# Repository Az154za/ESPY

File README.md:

# ESPY:
The main mcu is the esp32-P4 that allows fast lane data transmission allowing the camera and display option .
This project contains 4 layers 2 for signals 1 for 3V3 and one for Ground .  

The reason I chose the p4 is because it's very good for cameras .

-- feel free to grab gerber file and to print them yourself --
# Schematic :

# Routing :

# 3D overview : 

# BOM ( visual ) 

Total:192$

I hope you like this project

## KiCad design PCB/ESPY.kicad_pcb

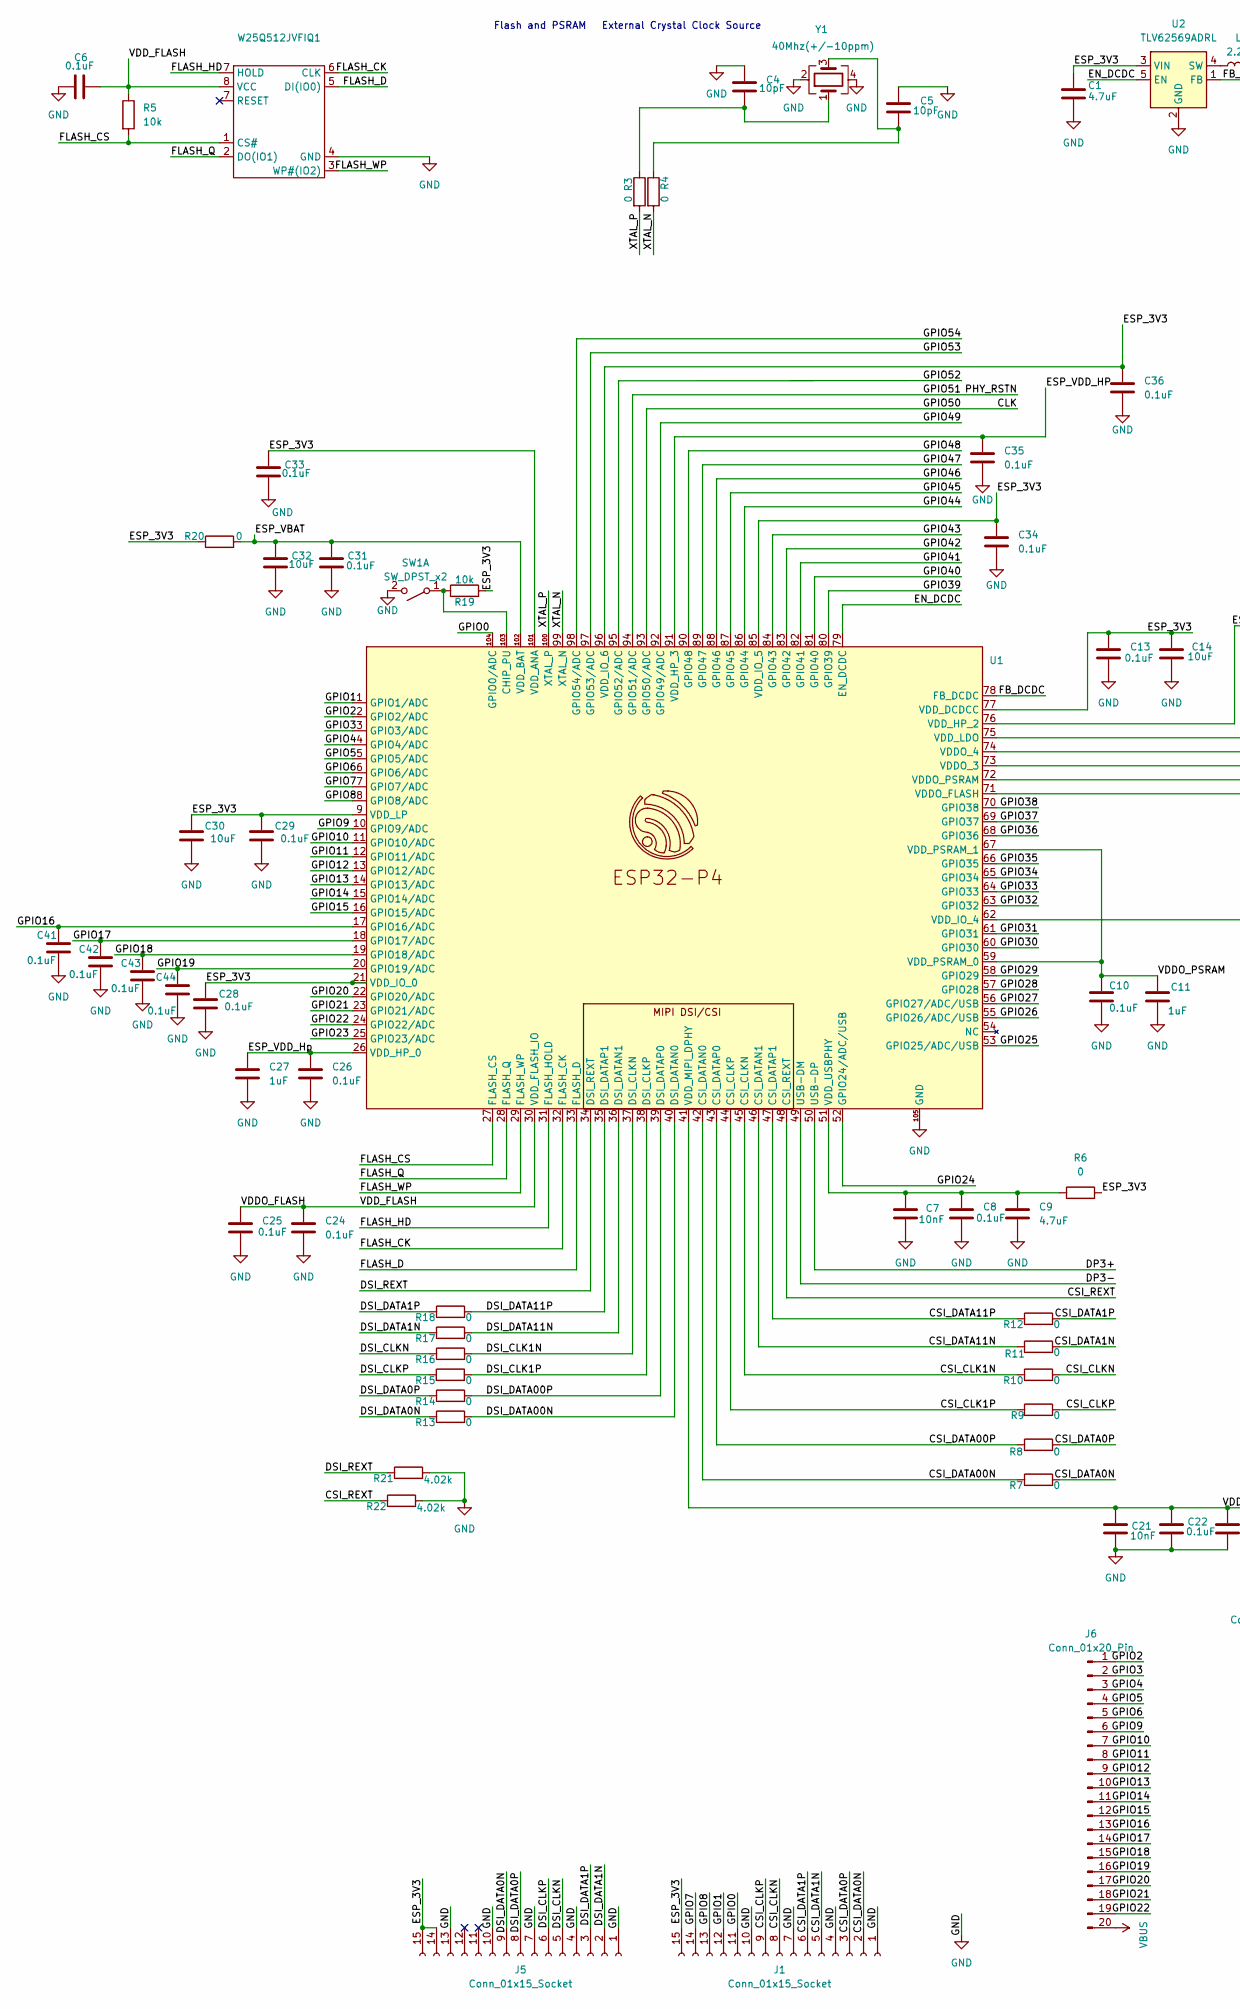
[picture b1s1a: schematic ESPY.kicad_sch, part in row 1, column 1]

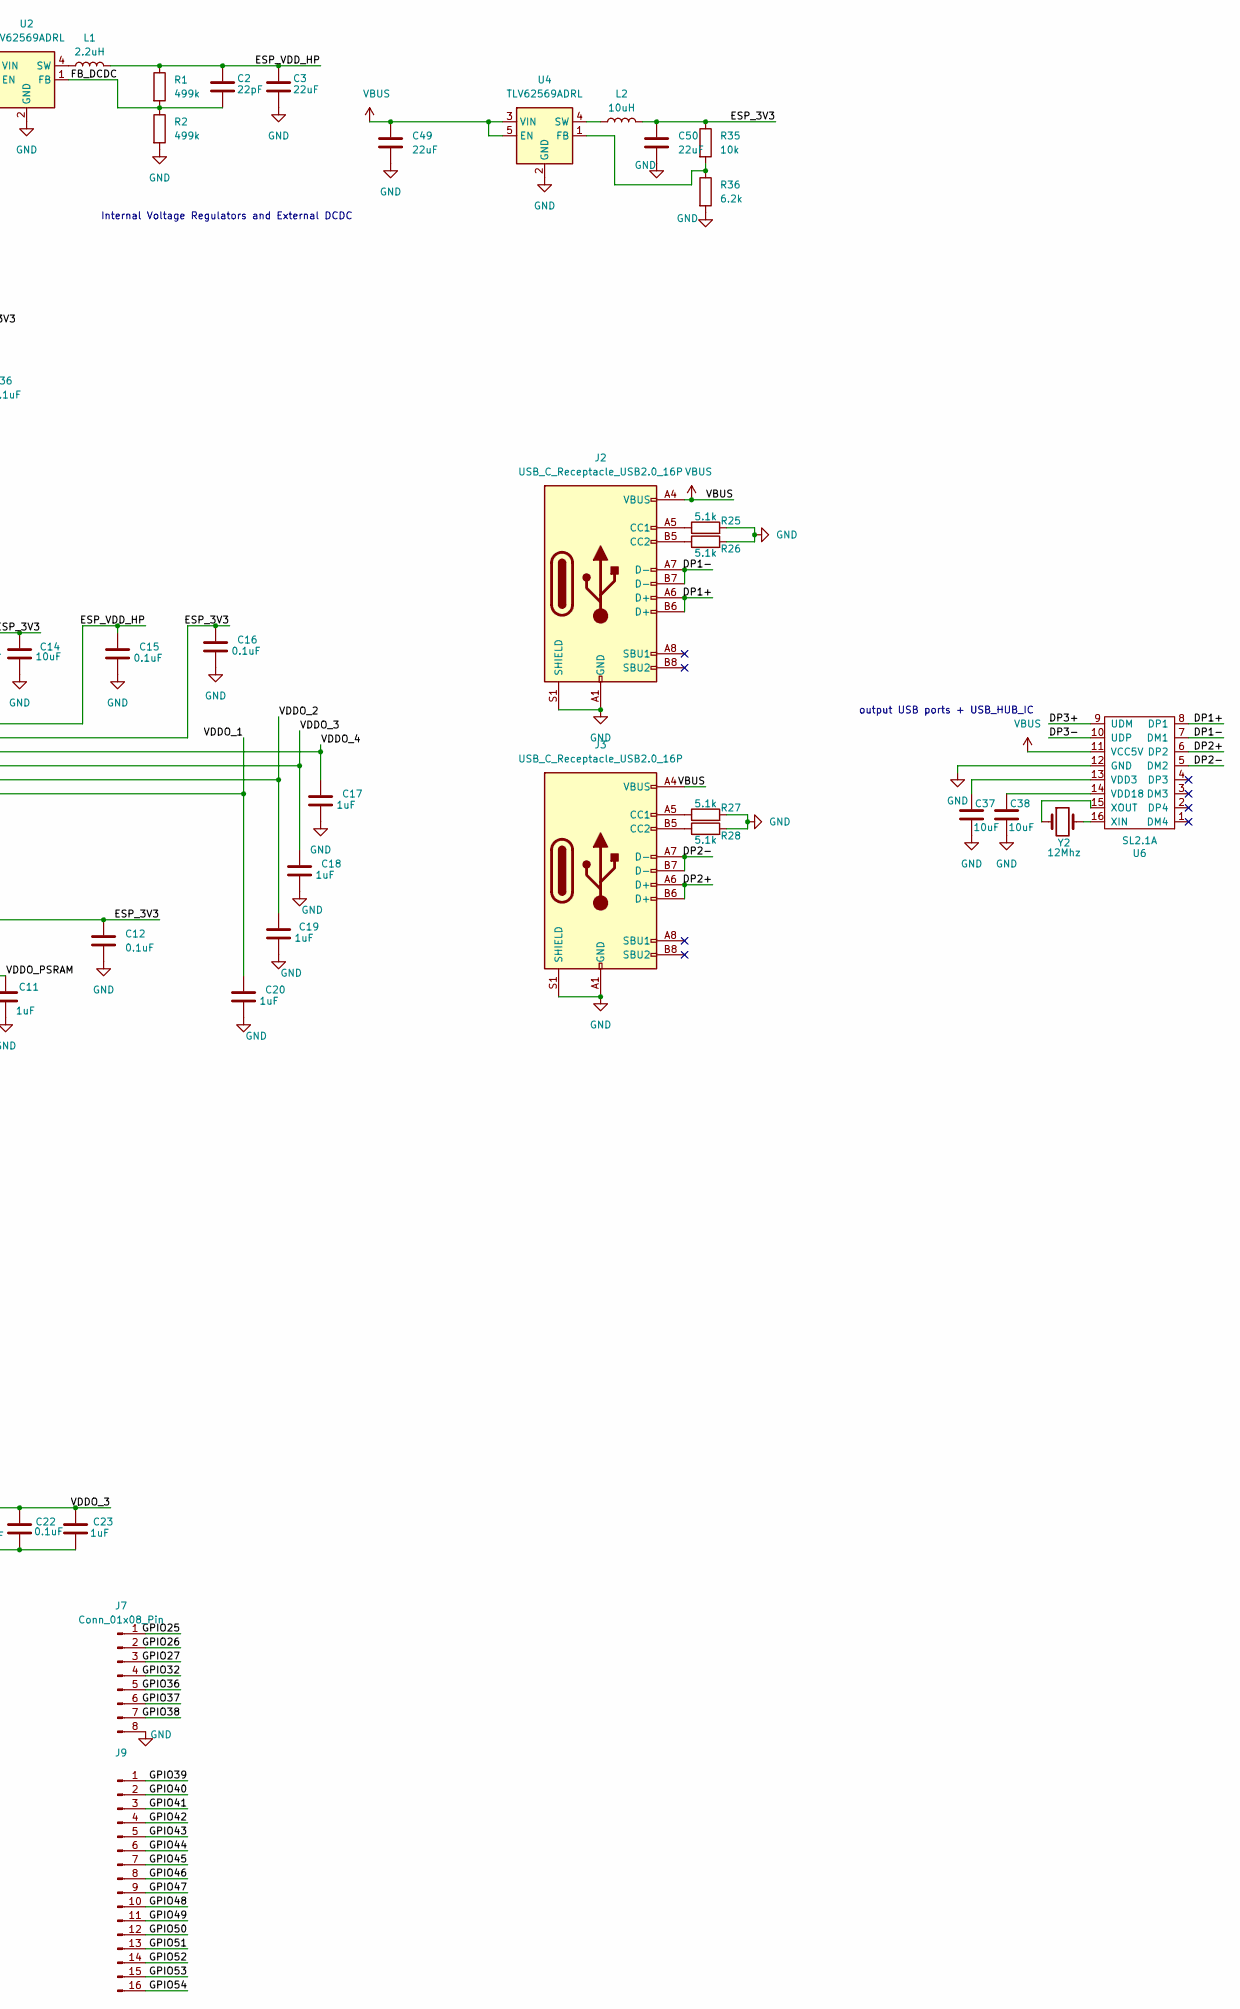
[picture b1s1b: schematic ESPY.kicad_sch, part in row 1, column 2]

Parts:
C1, C9: 4.7uF; C_0402_1005Metric
C2: 22pF; C_0402_1005Metric
C3, C49, C50: 22uF; C_0402_1005Metric
C4, C5: 10pF; C_0402_1005Metric
C6, C8, C10, C12, C13, C15, C16, C22, C24, C25, C26, C28, C29, C31, C33, C34, C35, C36, C41, C42, C43, C44: 0.1uF; C_0402_1005Metric
C7, C21: 10nF; C_0402_1005Metric
C11, C17, C18, C19, C20, C23, C27: 1uF; C_0402_1005Metric
C14, C30, C32, C37, C38: 10uF; C_0402_1005Metric
J1, J5: Conn_01x15_Socket; Molex_502244-1530_1x15-1MP_P0.5mm_Horizontal
J2, J3: USB_C_Receptacle_USB2.0_16P; USB_C_Receptacle_GCT_USB4105-xx-A_16P_TopMnt_Horizontal
J6: Conn_01x20_Pin; PinHeader_2x10_P2.54mm_Vertical
J7: Conn_01x08_Pin; PinHeader_1x08_P2.54mm_Vertical
J9: Conn_01x16_Pin; PinHeader_2x08_P2.54mm_Vertical
L1: 2.2uH; L_0402_1005Metric
L2: 10uH; L_0603_1608Metric
R1, R2: 499k; R_0402_1005Metric
R3, R4, R6, R7, R8, R9, R10, R11, R12, R13, R14, R15, R16, R17, R18, R20: 0; R_0402_1005Metric
R5, R19, R35: 10k; R_0402_1005Metric
R21, R22: 4.02k; R_0402_1005Metric
R25, R26, R27, R28: 5.1k; R_0402_1005Metric
R36: 6.2k; R_0402_1005Metric
SW1: SW_DPST_x2; SW_Push_SPST_NO_Alps_SKRK
U1: ESP32-P4
U2, U4: TLV62569ADRL; SOT-563
U6: SL2.1A; SOIC-16_4.55x10.3mm_P1.27mm
W25Q512JVFIQ1: SOIC-16W_7.5x10.3mm_P1.27mm
Y1: 40Mhz(+/-10ppm); Oscillator_SMD_Abracon_ASE-4Pin_3.2x2.5mm
Y2: 12Mhz; Crystal_SMD_3215-2Pin_3.2x1.5mm

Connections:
/CLK: J9.12, U1.93 (GPIO50/ADC)
/CSI_CLK1N: R10.1, U1.45 (CSI_CLKN)
/CSI_CLK1P: R9.1, U1.44 (CSI_CLKP)
/CSI_CLKN: J1.8, R10.2
/CSI_CLKP: J1.9, R9.2
/CSI_DATA00N: R7.1, U1.42 (CSI_DATAN0)
/CSI_DATA0N: J1.2, R7.2
/CSI_DATA00P: R8.1, U1.43 (CSI_DATAP0)
/CSI_DATA0P: J1.3, R8.2
/CSI_DATA1N: J1.5, R11.2
/CSI_DATA1P: J1.6, R12.2
/CSI_DATA11N: R11.1, U1.46 (CSI_DATAN1)
/CSI_DATA11P: R12.1, U1.47 (CSI_DATAP1)
/CSI_REXT: R22.1, U1.48 (CSI_REXT)
/DP1+: J2.A6 (D+), J2.B6 (D+), U6.8 (DP1)
/DP1-: J2.A7 (D-), J2.B7 (D-), U6.7 (DM1)
/DP2+: J3.A6 (D+), J3.B6 (D+), U6.6 (DP2)
/DP2-: J3.A7 (D-), J3.B7 (D-), U6.5 (DM2)
/DP3+: U1.50 (USB-DP), U6.9 (UDM)
/DP3-: U1.49 (USB-DM), U6.10 (UDP)
/DSI_CLK1N: R16.2, U1.37 (DSI_CLKN)
/DSI_CLK1P: R15.2, U1.38 (DSI_CLKP)
/DSI_CLKN: J5.5, R16.1
/DSI_CLKP: J5.6, R15.1
/DSI_DATA0N: J5.9, R13.1
/DSI_DATA00N: R13.2, U1.40 (DSI_DATAN0)
/DSI_DATA0P: J5.8, R14.1
/DSI_DATA00P: R14.2, U1.39 (DSI_DATAP0)
/DSI_DATA1N: J5.2, R17.1
/DSI_DATA1P: J5.3, R18.1
/DSI_DATA11N: R17.2, U1.36 (DSI_DATAN1)
/DSI_DATA11P: R18.2, U1.35 (DSI_DATAP1)
/DSI_REXT: R21.1, U1.34 (DSI_REXT)
/EN_DCDC: U1.79 (EN_DCDC), U2.5 (EN)
/ESP_3V3: C1.1, C12.1, C13.1, C14.1, C16.1, C28.1, C29.1, C30.1, C33.1, C34.1, C36.1, C50.1, J1.15, J5.14, J5.15, L2.2, R6.2, R19.2, R20.1, R35.1, U1.9 (VDD_LP), U1.21 (VDD_IO_0), U1.62 (VDD_IO_4), U1.75 (VDD_LDO), U1.77 (VDD_DCDCC), U1.85 (VDD_IO_5), U1.96 (VDD_IO_6), U1.101 (VDD_ANA), U2.3 (VIN)
/ESP_VBAT: C31.1, C32.1, R20.2, U1.102 (VDD_BAT)
/ESP_VDD_HP: C2.1, C3.1, C15.1, C35.1, L1.2, R1.1, U1.76 (VDD_HP_2), U1.91 (VDD_HP_3)
/ESP_VDD_Hp: C26.1, C27.1, U1.26 (VDD_HP_0)
/FB_DCDC: C2.2, R1.2, R2.1, U1.78 (FB_DCDC), U2.1 (FB)
/FLASH_CK: U1.32 (FLASH_CK), W25Q512JVFIQ1.6 (CLK)
/FLASH_CS: R5.2, U1.27 (FLASH_CS), W25Q512JVFIQ1.1 (CS#)
/FLASH_D: U1.33 (FLASH_D), W25Q512JVFIQ1.5 (DI(IO0))
/FLASH_HD: U1.31 (FLASH_HOLD), W25Q512JVFIQ1.7 (HOLD)
/FLASH_Q: U1.28 (FLASH_Q), W25Q512JVFIQ1.2 (DO(IO1))
/FLASH_WP: U1.29 (FLASH_WP), W25Q512JVFIQ1.3 (WP#(IO2))
/GPIO0: J1.11, U1.104 (GPIO0/ADC)
/GPIO1: J1.12, U1.1 (GPIO1/ADC)
/GPIO2: J6.1, U1.2 (GPIO2/ADC)
/GPIO3: J6.2, U1.3 (GPIO3/ADC)
/GPIO4: J6.3, U1.4 (GPIO4/ADC)
/GPIO5: J6.4, U1.5 (GPIO5/ADC)
/GPIO6: J6.5, U1.6 (GPIO6/ADC)
/GPIO7: J1.14, U1.7 (GPIO7/ADC)
/GPIO8: J1.13, U1.8 (GPIO8/ADC)
/GPIO9: J6.6, U1.10 (GPIO9/ADC)
/GPIO10: J6.7, U1.11 (GPIO10/ADC)
/GPIO11: J6.8, U1.12 (GPIO11/ADC)
/GPIO12: J6.9, U1.13 (GPIO12/ADC)
/GPIO13: J6.10, U1.14 (GPIO13/ADC)
/GPIO14: J6.11, U1.15 (GPIO14/ADC)
/GPIO15: J6.12, U1.16 (GPIO15/ADC)
/GPIO16: C41.1, J6.13, U1.17 (GPIO16/ADC)
/GPIO17: C42.1, J6.14, U1.18 (GPIO17/ADC)
/GPIO18: C43.1, J6.15, U1.19 (GPIO18/ADC)
/GPIO19: C44.1, J6.16, U1.20 (GPIO19/ADC)
/GPIO20: J6.17, U1.22 (GPIO20/ADC)
/GPIO21: J6.18, U1.23 (GPIO21/ADC)
/GPIO22: J6.19, U1.24 (GPIO22/ADC)
/GPIO23: U1.25 (GPIO23/ADC)
/GPIO24: U1.52 (GPIO24/ADC/USB)
/GPIO25: J7.1, U1.53 (GPIO25/ADC/USB)
/GPIO26: J7.2, U1.55 (GPIO26/ADC/USB)
/GPIO27: J7.3, U1.56 (GPIO27/ADC/USB)
/GPIO28: U1.57 (GPIO28)
/GPIO29: U1.58 (GPIO29)
/GPIO30: U1.60 (GPIO30)
/GPIO31: U1.61 (GPIO31)
/GPIO32: J7.4, U1.63 (GPIO32)
/GPIO33: U1.64 (GPIO33)
/GPIO34: U1.65 (GPIO34)
/GPIO35: U1.66 (GPIO35)
/GPIO36: J7.5, U1.68 (GPIO36)
/GPIO37: J7.6, U1.69 (GPIO37)
/GPIO38: J7.7, U1.70 (GPIO38)
/GPIO39: J9.1, U1.80 (GPIO39)
/GPIO40: J9.2, U1.81 (GPIO40)
/GPIO41: J9.3, U1.82 (GPIO41)
/GPIO42: J9.4, U1.83 (GPIO42)
/GPIO43: J9.5, U1.84 (GPIO43)
/GPIO44: J9.6, U1.86 (GPIO44)
/GPIO45: J9.7, U1.87 (GPIO45)
/GPIO46: J9.8, U1.88 (GPIO46)
/GPIO47: J9.9, U1.89 (GPIO47)
/GPIO48: J9.10, U1.90 (GPIO48)
/GPIO49: J9.11, U1.92 (GPIO49/ADC)
/GPIO51: J9.13, U1.94 (GPIO51/ADC)
/GPIO52: J9.14, U1.95 (GPIO52/ADC)
/GPIO53: J9.15, U1.97 (GPIO53/ADC)
/GPIO54: J9.16, U1.98 (GPIO54/ADC)
/VDDO_1: C20.1, U1.71 (VDDO_FLASH)
/VDDO_2: C19.1, U1.72 (VDDO_PSRAM)
/VDDO_3: C18.1, C21.1, C22.1, C23.1, U1.41 (VDD_MIPI_DPHY), U1.73 (VDDO_3)
/VDDO_4: C17.1, U1.74 (VDDO_4)
/VDDO_FLASH: C6.1, C24.1, C25.1, R5.1, U1.30 (VDD_FLASH_IO), W25Q512JVFIQ1.8 (VCC)
/VDDO_PSRAM: C10.1, C11.1, U1.59 (VDD_PSRAM_0), U1.67 (VDD_PSRAM_1)
/XTAL_N: R4.2, U1.99 (XTAL_N)
/XTAL_P: R3.2, U1.100 (XTAL_P)
GND: C1.2, C3.2, C4.1, C5.1, C6.2, C7.2, C8.2, C9.2, C10.2, C11.2, C12.2, C13.2, C14.2, C15.2, C16.2, C17.2, C18.2, C19.2, C20.2, C21.2, C22.2, C23.2, C24.2, C25.2, C26.2, C27.2, C28.2, C29.2, C30.2, C31.2, C32.2, C33.2, C34.2, C35.2, C36.2, C37.2, C38.2, C41.2, C42.2, C43.2, C44.2, C49.2, C50.2, J1.1, J1.4, J1.7, J1.10, J2.A1 (GND), J2.A12 (GND), J2.B1 (GND), J2.B12 (GND), J2.S1 (SHIELD), J3.A1 (GND), J3.A12 (GND), J3.B1 (GND), J3.B12 (GND), J3.S1 (SHIELD), J5.1, J5.4, J5.7, J5.10, J5.13, J7.8, R2.2, R21.2, R22.2, R25.2, R26.2, R27.2, R28.2, R36.2, SW1.2 (B), U1.105 (GND), U2.2 (GND), U4.2 (GND), U6.12 (GND), W25Q512JVFIQ1.4 (GND), Y1.2, Y1.4
unnamed: C4.2, R3.1, Y1.1
unnamed: C5.2, R4.1, Y1.3
unnamed: J2.A5 (CC1), R25.1
unnamed: J2.B5 (CC2), R26.1
unnamed: J3.A5 (CC1), R27.1
unnamed: J3.B5 (CC2), R28.1
unnamed: R19.1, SW1.1 (A), U1.103 (CHIP_PU)
unnamed: C7.1, C8.1, C9.1, R6.1, U1.51 (VDD_USBPHY)
unnamed: L1.1, U2.4 (SW)
unnamed: R35.2, R36.1, U4.1 (FB)
unnamed: L2.1, U4.4 (SW)
unnamed: C37.1, U6.13 (VDD3)
unnamed: C38.1, U6.14 (VDD18)
unnamed: U6.16 (XIN), Y2.2
unnamed: U6.15 (XOUT), Y2.1
VBUS: C49.1, J2.A4 (VBUS), J2.A9 (VBUS), J2.B4 (VBUS), J2.B9 (VBUS), J3.A4 (VBUS), J3.A9 (VBUS), J3.B4 (VBUS), J3.B9 (VBUS), J6.20, U4.3 (VIN), U4.5 (EN), U6.11 (VCC5V)

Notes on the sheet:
Flash and PSRAM
External Crystal Clock Source
output USB ports + USB_HUB_IC
Internal Voltage Regulators and External DCDC

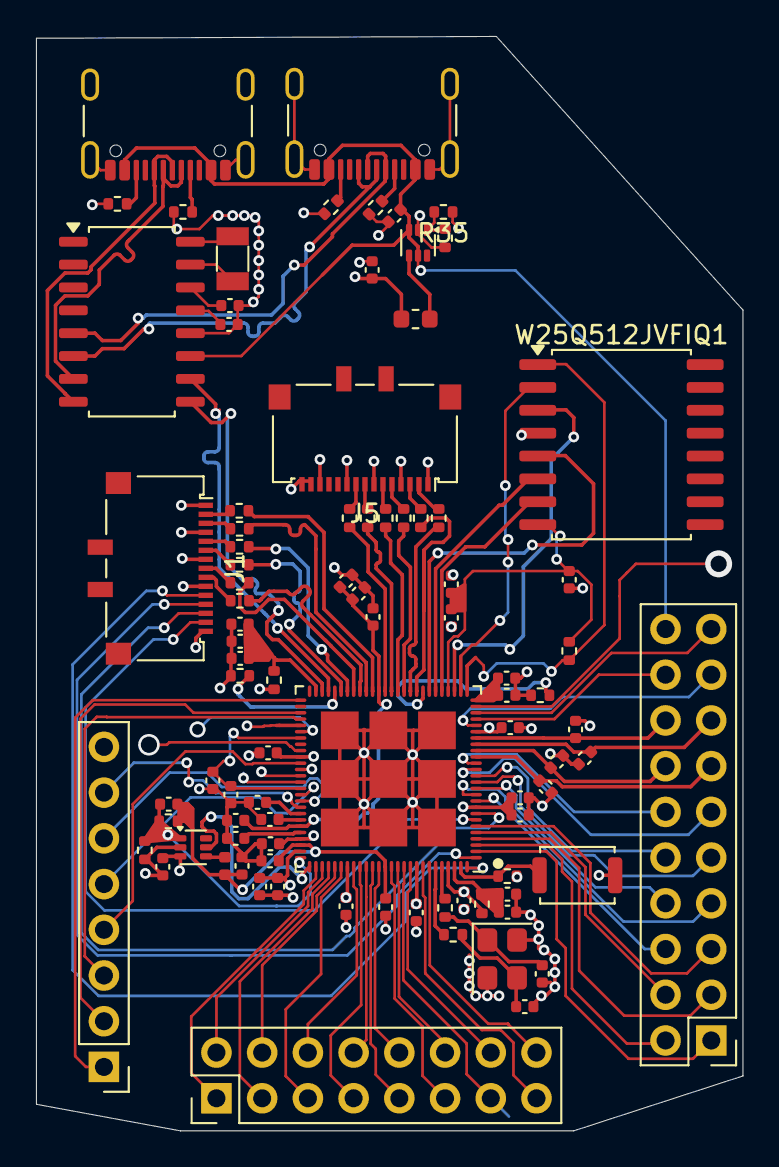
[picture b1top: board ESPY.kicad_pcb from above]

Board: 4 copper layers, 39.2 x 60.8 mm, 89 parts (0 on the bottom side), 115 nets.

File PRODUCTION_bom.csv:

Designator,Footprint,Quantity,Value,LCSC Part #
"C1, C9",0402,2,4.7uF,
"C10, C12, C13, C15, C16, C22, C24, C25, C26, C28, C29, C31, C33, C34, C35, C36, C41, C42, C43, C44, C6, C8",0402,22,0.1uF,
"C11, C17, C18, C19, C20, C23, C27",0402,7,1uF,
"C14, C30, C32, C37, C38",0402,5,10uF,
C2,0402,1,22pF,
"C21, C7",0402,2,10nF,
"C3, C49, C50",0402,3,22uF,
"C4, C5",0402,2,10pF,
"J1, J5",Molex_502244-1530_1x15-1MP_P0.5mm_Horizontal,2,Conn_01x15_Socket,
"J2, J3",USB_C_Receptacle_GCT_USB4105-xx-A_16P_TopMnt_Horizontal,2,USB_C_Receptacle_USB2.0_16P,
J6,PinHeader_2x10_P2.54mm_Vertical,1,Conn_01x20_Pin,
J7,PinHeader_1x08_P2.54mm_Vertical,1,Conn_01x08_Pin,
J9,PinHeader_2x08_P2.54mm_Vertical,1,Conn_01x16_Pin,
L1,0402,1,2.2uH,
L2,0603,1,10uH,
"R1, R2",0402,2,499k,
"R10, R11, R12, R13, R14, R15, R16, R17, R18, R20, R3, R4, R6, R7, R8, R9",0402,16,0,
"R19, R35, R5",0402,3,10k,
"R21, R22",0402,2,4.02k,
"R25, R26, R27, R28",0402,4,5.1k,
R36,0402,1,6.2k,
SW1,SW_Push_SPST_NO_Alps_SKRK,1,SW_DPST_x2,
U1,ESP32-P4,1,~,
"U2, U4",SOT-563,2,TLV62569ADRL,
U6,SOIC-16_4.55x10.3mm_P1.27mm,1,SL2.1A,
W25Q512JVFIQ1,SOIC-16W_7.5x10.3mm_P1.27mm,1,~,
Y1,Oscillator_SMD_Abracon_ASE-4Pin_3.2x2.5mm,1,40Mhz(+/-10ppm),
Y2,Crystal_SMD_3215-2Pin_3.2x1.5mm,1,12Mhz,

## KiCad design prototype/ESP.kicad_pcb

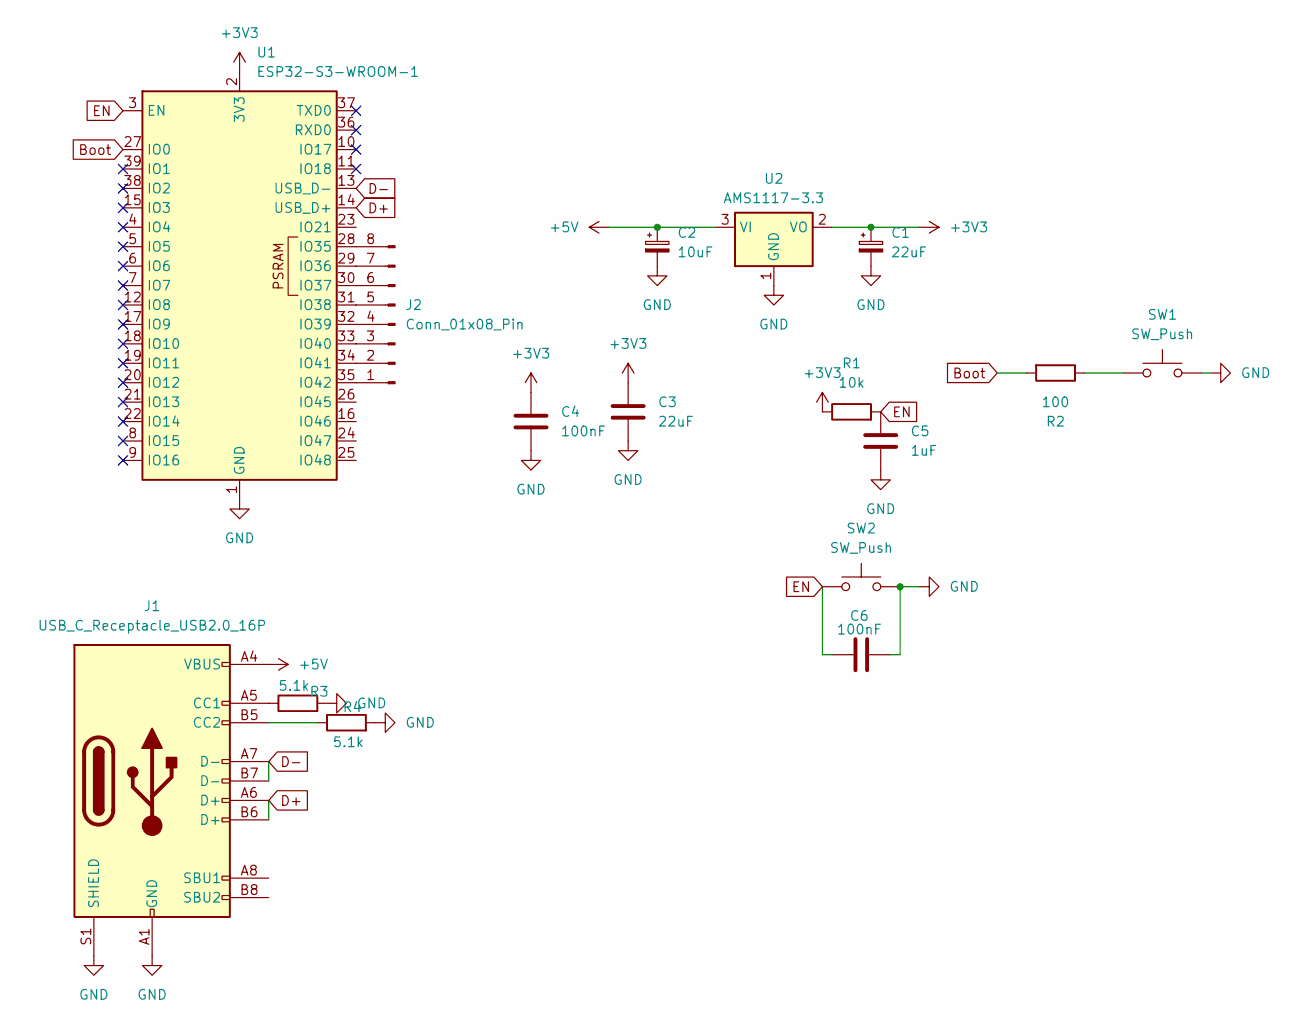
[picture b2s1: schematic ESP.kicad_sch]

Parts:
C1, C3: 22uF; C_0805_2012Metric_Pad1.18x1.45mm_HandSolder
C2: 10uF; C_0805_2012Metric_Pad1.18x1.45mm_HandSolder
C4, C6: 100nF; C_0805_2012Metric_Pad1.18x1.45mm_HandSolder
C5: 1uF; C_0805_2012Metric_Pad1.18x1.45mm_HandSolder
J1: USB_C_Receptacle_USB2.0_16P; USB_C_Receptacle_HRO_TYPE-C-31-M-12
J2: Conn_01x08_Pin; PinHeader_1x08_P1.00mm_Vertical
R1: 10k; R_0805_2012Metric_Pad1.20x1.40mm_HandSolder
R2: 100; R_0805_2012Metric_Pad1.20x1.40mm_HandSolder
R3, R4: 5.1k; R_0805_2012Metric_Pad1.20x1.40mm_HandSolder
SW1, SW2: SW_Push; SW_SPST_B3U-1000P-B
U1: ESP32-S3-WROOM-1
U2: AMS1117-3.3; SOT-223-3_TabPin2

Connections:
+3V3: C1.1, C3.1, C4.1, R1.1, U1.2 (3V3), U2.2 (VO)
+5V: C2.1, J1.A4 (VBUS), J1.A9 (VBUS), J1.B4 (VBUS), J1.B9 (VBUS), U2.3 (VI)
Boot: R2.2, U1.27 (IO0)
D+: J1.A6 (D+), J1.B6 (D+), U1.14 (USB_D+)
D-: J1.A7 (D-), J1.B7 (D-), U1.13 (USB_D-)
EN: C5.1, C6.1, R1.2, SW2.1, U1.3 (EN)
GND: C1.2, C2.2, C3.2, C4.2, C5.2, C6.2, J1.A1 (GND), J1.A12 (GND), J1.B1 (GND), J1.B12 (GND), J1.S1 (SHIELD), R3.2, R4.2, SW1.2, SW2.2, U1.1 (GND), U1.40 (GND), U1.41 (GND), U2.1 (GND)
unnamed: J1.A5 (CC1), R3.1
unnamed: J1.B5 (CC2), R4.1
unnamed: J2.1, U1.35 (IO42)
unnamed: J2.2, U1.34 (IO41)
unnamed: J2.3, U1.33 (IO40)
unnamed: J2.4, U1.32 (IO39)
unnamed: J2.5, U1.31 (IO38)
unnamed: J2.6, U1.30 (IO37)
unnamed: J2.7, U1.29 (IO36)
unnamed: J2.8, U1.28 (IO35)
unnamed: R2.1, SW1.1

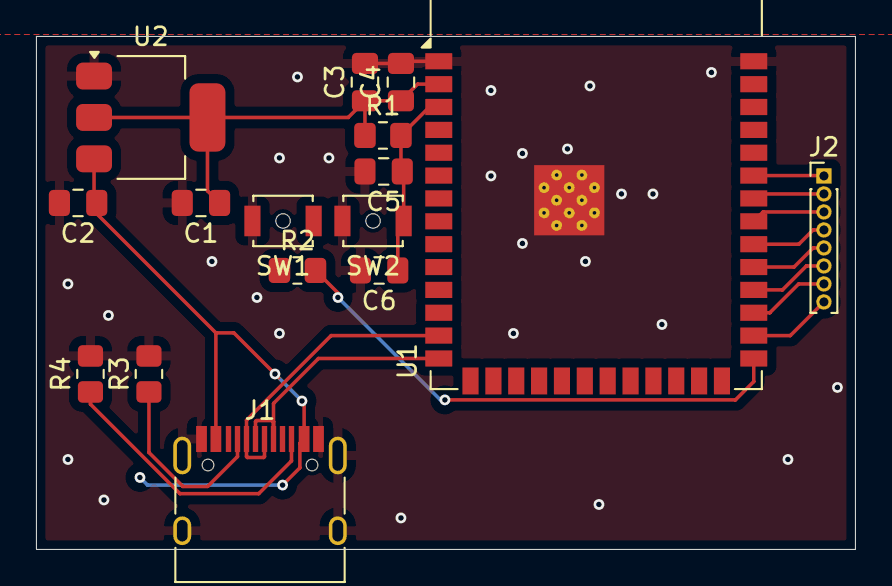
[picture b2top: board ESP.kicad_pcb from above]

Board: 2 copper layers, 45.5 x 28.5 mm, 16 parts (0 on the bottom side), 18 nets.

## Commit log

2026-04-21 Update README with project details and schematic
    Added project description and schematic image to README.
2026-05-07 Saved my files
2026-05-08 files saved
